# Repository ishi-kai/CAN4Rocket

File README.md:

# CAN Base Board for Rocket
CAN Base Board for Rocket.
The power supply section and the CAN communication section are insulated.

## Base System
This is a version with a universal board attached to the CAN base board.  
- [CAN_Isolation](./CAN_Isolation/)
- 

## Mini System
This is a mini version of the baseboard.  

- [CAN_Isolation_mini](./CAN_Isolation_mini/)
- [CAN_Isolation_mini_3.3V](./CAN_Isolation_mini_3.3V/)
- 

## High-Current Board for Servos System
This is a board with an XT60 connector for servos added to the mini version.  

- [CAN_Isolation_mini_XT60](./CAN_Isolation_mini_XT60/)
- [CAN_Isolation_mini_XT60_3.3V](./CAN_Isolation_mini_XT60_3.3V/)
-

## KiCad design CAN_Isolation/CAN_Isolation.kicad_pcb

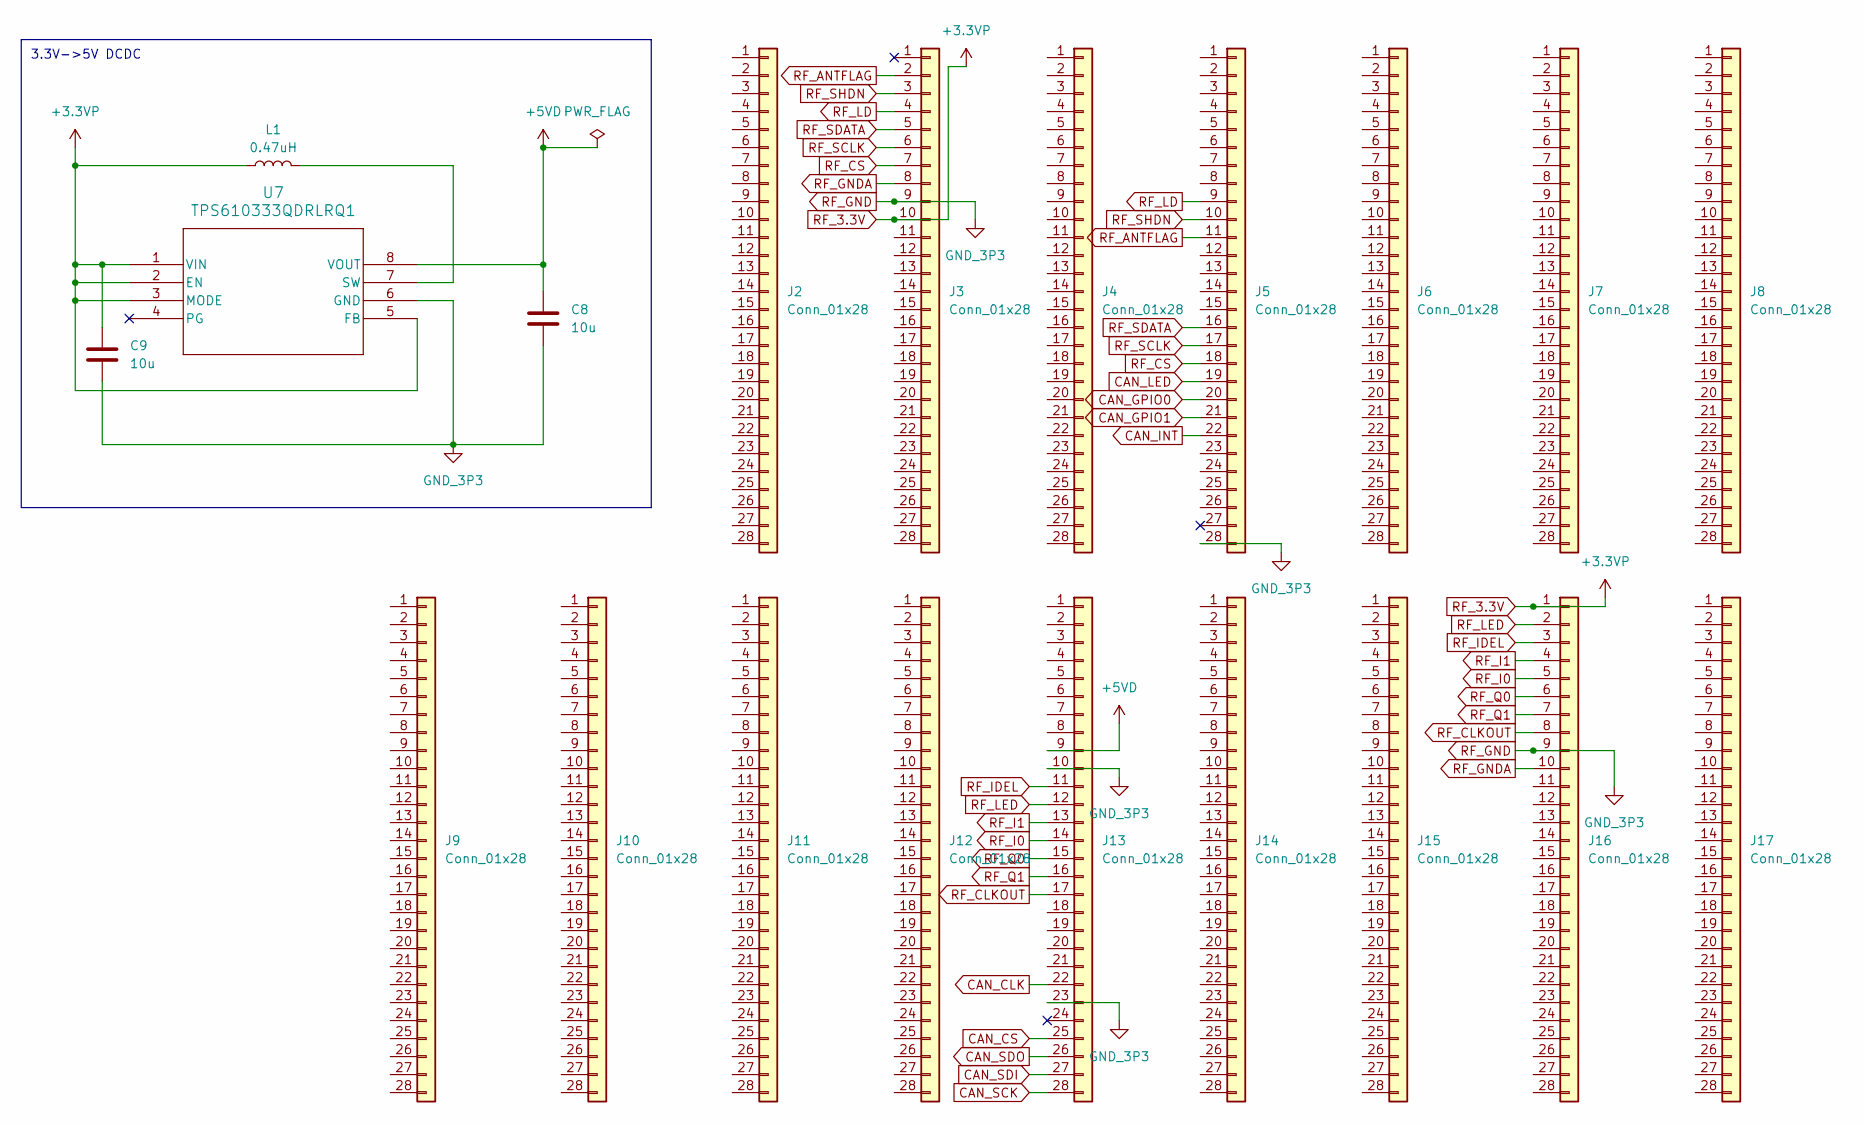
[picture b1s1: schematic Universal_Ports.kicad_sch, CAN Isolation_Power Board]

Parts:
C8, C9: 10u; C_0603_1608Metric
J2, J3, J4, J5, J6, J7, J8, J9, J10, J11, J12, J13, J14, J15, J16, J17: Conn_01x28; PinHeader_1x28_P2.54mm_NoSilkScreen
L1: 0.47uH; IND_LCCN_1608KK_TAY
U7: TPS610333QDRLRQ1; SOT-5X3-8_DRL_TEX

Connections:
+5VD: C8.1, J13.9, U7.8 (VOUT)
CAN_CLK: J13.22; also elsewhere on the board
CAN_CS: J13.25; also elsewhere on the board
CAN_GPIO0: J5.20; also elsewhere on the board
CAN_GPIO1: J5.21; also elsewhere on the board
CAN_INT: J5.22; also elsewhere on the board
CAN_LED: J5.19; also elsewhere on the board
CAN_SCK: J13.28; also elsewhere on the board
CAN_SDI: J13.27; also elsewhere on the board
CAN_SDO: J13.26; also elsewhere on the board
unnamed: L1.2, U7.7 (SW)
RF_3.3V: C9.1, J3.10, J16.1, L1.1, U7.1 (VIN), U7.2 (EN), U7.3 (MODE), U7.5 (FB); also elsewhere on the board
RF_ANTFLAG: J3.2, J5.11
RF_CLKOUT: J13.17, J16.8
RF_CS: J3.7, J5.18
RF_GND: C8.2, C9.2, J3.9, J5.28, J13.10, J13.23, J16.9, U7.6 (GND); also elsewhere on the board
RF_GNDA: J3.8, J16.10
RF_I0: J13.14, J16.5
RF_I1: J13.13, J16.4
RF_IDEL: J13.11, J16.3
RF_LD: J3.4, J5.9
RF_LED: J13.12, J16.2
RF_Q0: J13.15, J16.6
RF_Q1: J13.16, J16.7
RF_SCLK: J3.6, J5.17
RF_SDATA: J3.5, J5.16
RF_SHDN: J3.3, J5.10

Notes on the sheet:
3.3V->5V DCDC

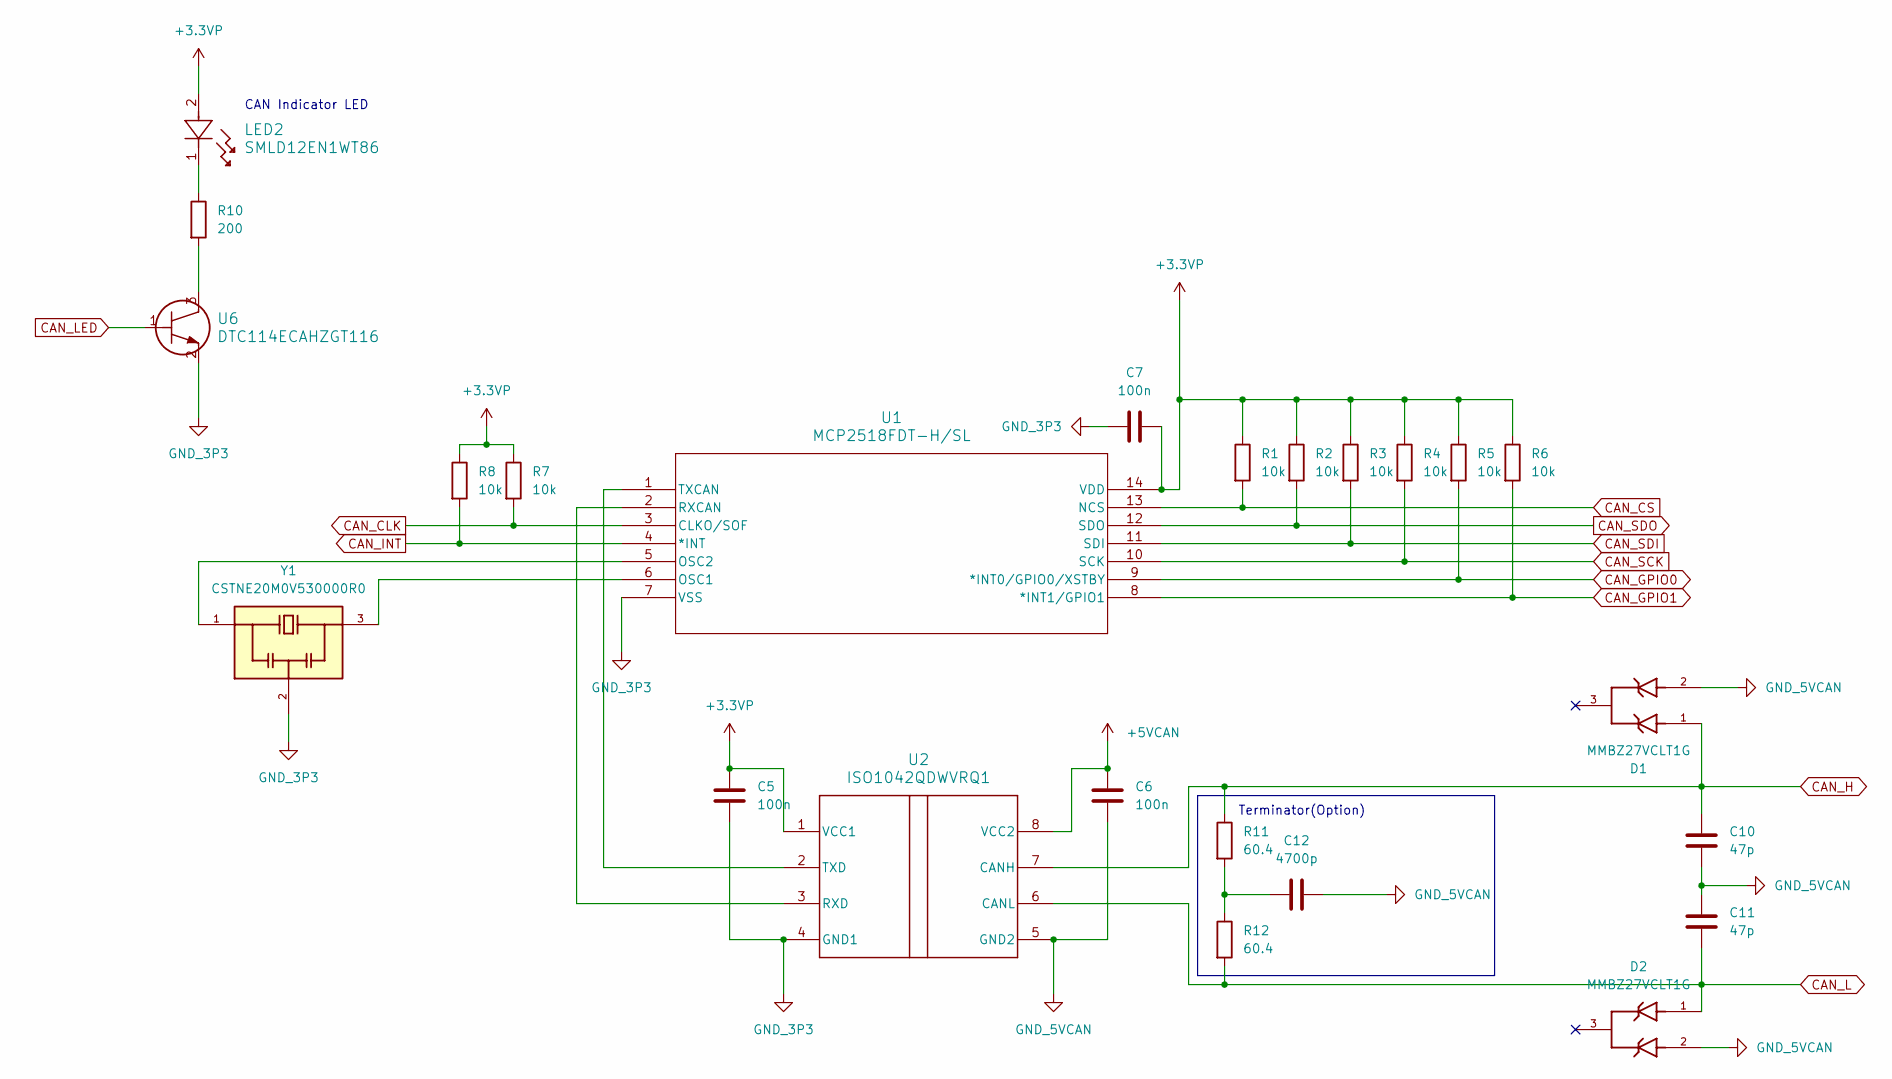
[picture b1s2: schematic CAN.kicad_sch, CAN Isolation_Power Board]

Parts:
C5, C6, C7: 100n; C_0603_1608Metric
C10, C11: 47p; C_0603_1608Metric
C12: 4700p; C_0603_1608Metric
D1, D2: MMBZ27VCLT1G; SOT95P237X111-3N; PARTREV 17
LED2: SMLD12EN1WT86
R1, R2, R3, R4, R5, R6, R7, R8: 10k; R_0603_1608Metric
R10: 200; R_0603_1608Metric
R11, R12: 60.4; R_Axial_DIN0207_L6.3mm_D2.5mm_P7.62mm_Horizontal
U1: MCP2518FDT-H/SL; SOIC14_150MIL_SL_MCH
U2: ISO1042QDWVRQ1; DWV0008A-IPC_A
U6: DTC114ECAHZGT116; TRANS_DTCZCAHZGT_ROM
Y1: CSTNE20M0V530000R0; OSC_CSTNE20M0V530000R0; PARTREV JGC42-8853B

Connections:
+5VCAN: C6.1, U2.8 (VCC2); also elsewhere on the board
CAN_CLK: R7.2, U1.3 (CLKO/SOF); also elsewhere on the board
CAN_CS: R1.2, U1.13 (NCS); also elsewhere on the board
CAN_GPIO0: R5.2, U1.9 (*INT0/GPIO0/XSTBY); also elsewhere on the board
CAN_GPIO1: R6.2, U1.8 (*INT1/GPIO1); also elsewhere on the board
CAN_H: C10.1, D1.1, R11.1, U2.7 (CANH); also elsewhere on the board
CAN_INT: R8.2, U1.4 (*INT); also elsewhere on the board
CAN_L: C11.2, D2.1, R12.2, U2.6 (CANL); also elsewhere on the board
CAN_LED: U6.1; also elsewhere on the board
CAN_SCK: R4.2, U1.10 (SCK); also elsewhere on the board
CAN_SDI: R3.2, U1.11 (SDI); also elsewhere on the board
CAN_SDO: R2.2, U1.12 (SDO); also elsewhere on the board
GND_5VCAN: C6.2, C10.2, C11.1, C12.2, D1.2, D2.2, U2.5 (GND2); also elsewhere on the board
unnamed: C12.1, R11.2, R12.1
unnamed: LED2.1, R10.1
unnamed: R10.2, U6.3
unnamed: U1.6 (OSC1), Y1.3
unnamed: U1.5 (OSC2), Y1.1
unnamed: U1.2 (RXCAN), U2.3 (RXD)
unnamed: U1.1 (TXCAN), U2.2 (TXD)
RF_3.3V: C5.1, C7.2, LED2.2, R1.1, R2.1, R3.1, R4.1, R5.1, R6.1, R7.1, R8.1, U1.14 (VDD), U2.1 (VCC1); also elsewhere on the board
RF_GND: C5.2, C7.1, U1.7 (VSS), U2.4 (GND1), U6.2, Y1.2; also elsewhere on the board

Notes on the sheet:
CAN Indicator LED
Terminator(Option)

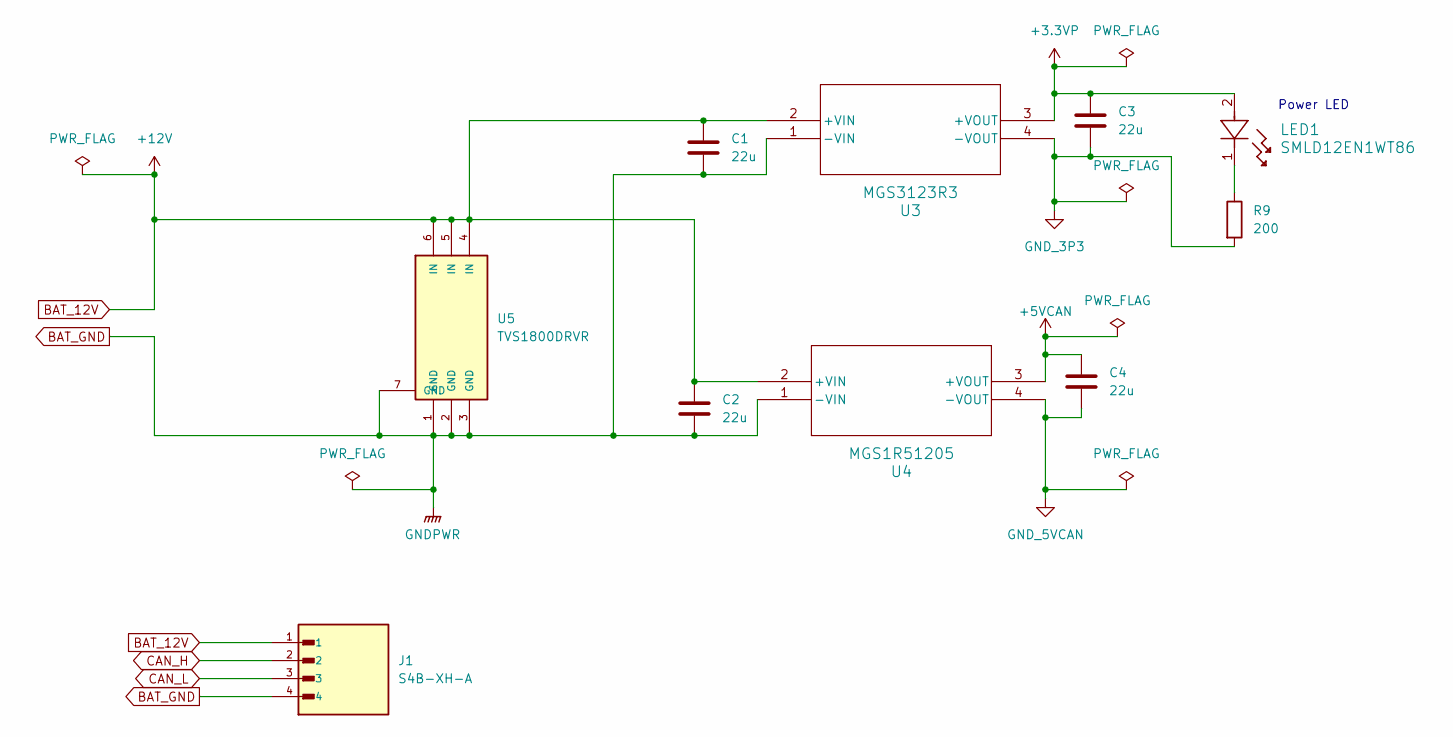
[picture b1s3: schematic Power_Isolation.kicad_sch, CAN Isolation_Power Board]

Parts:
C1, C2, C3, C4: 22u; C_1210_3225Metric
J1: S4B-XH-A; JST_S4B-XH-A
LED1: SMLD12EN1WT86
R9: 200; R_0603_1608Metric
U3: MGS3123R3; MGS3_COS
U4: MGS1R51205; MGS3_COS
U5: TVS1800DRVR; SON65P200X200X80-7N; PARTREV C

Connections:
+5VCAN: C4.1, U4.3 (+VOUT); also elsewhere on the board
BAT_12V: C1.1, C2.1, J1.1, U3.2 (+VIN), U4.2 (+VIN), U5.4 (IN), U5.5 (IN), U5.6 (IN)
BAT_GND: C1.2, C2.2, J1.4, U3.1 (-VIN), U4.1 (-VIN), U5.1 (GND), U5.2 (GND), U5.3 (GND), U5.7 (GND)
CAN_H: J1.2; also elsewhere on the board
CAN_L: J1.3; also elsewhere on the board
GND_5VCAN: C4.2, U4.4 (-VOUT); also elsewhere on the board
unnamed: LED1.1, R9.1
RF_3.3V: C3.1, LED1.2, U3.3 (+VOUT); also elsewhere on the board
RF_GND: C3.2, R9.2, U3.4 (-VOUT); also elsewhere on the board

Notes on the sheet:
Power LED

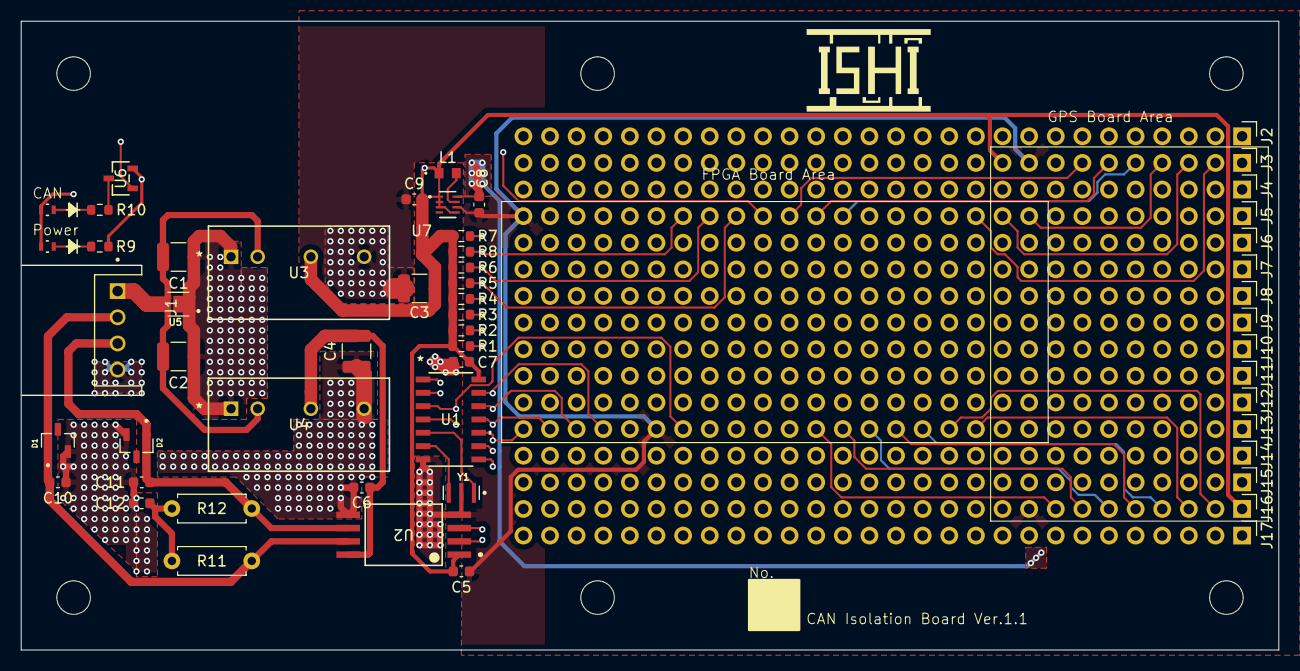
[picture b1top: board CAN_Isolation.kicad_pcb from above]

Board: 4 copper layers, 120.0 x 60.0 mm, 54 parts (0 on the bottom side), 41 nets.

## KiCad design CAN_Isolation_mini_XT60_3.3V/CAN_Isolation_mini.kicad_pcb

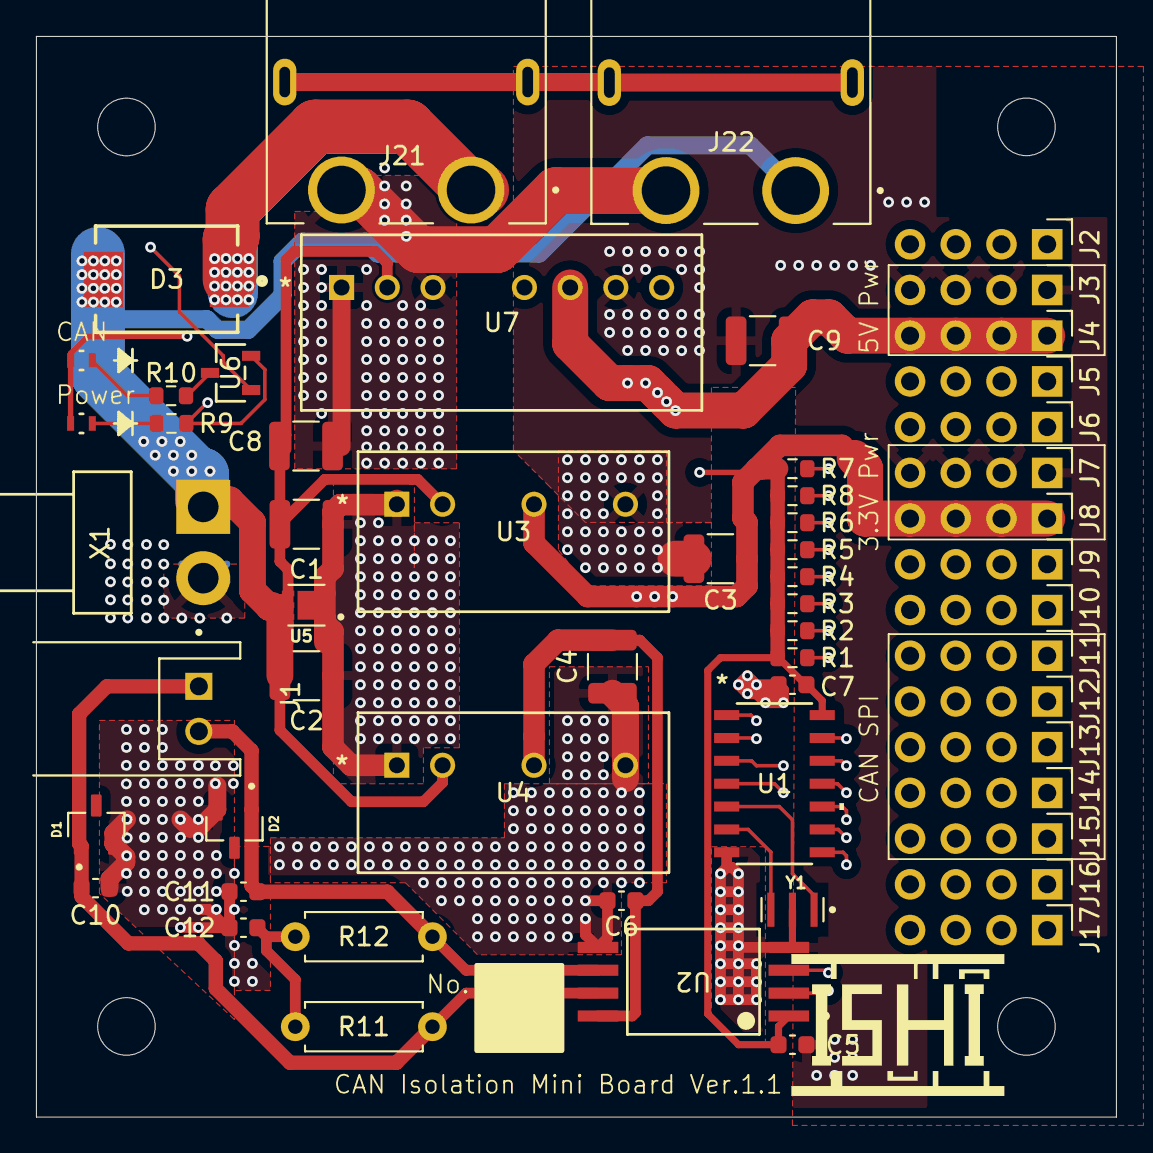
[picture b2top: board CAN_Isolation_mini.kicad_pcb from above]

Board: 4 copper layers, 60.0 x 60.0 mm, 57 parts (0 on the bottom side), 27 nets.

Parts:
C1, C2, C3, C4, C8, C9: 22u; C_1210_3225Metric
C5, C6, C7: 100n; C_0603_1608Metric
C10, C11: 47p; C_0603_1608Metric
C12: 4700p; C_0603_1608Metric
D1, D2: MMBZ27VCLT1G; SOT95P237X111-3N
D3: B520CQ-13-F; DIOM7959X250N
J1: S2B-XH-A; JST_S2B-XH-A
J2, J3, J4, J5, J6, J7, J8, J9, J10, J11, J12, J13, J14, J15, J16, J17: Conn_01x04_Pin; PinHeader_1x04_P2.54mm_Vertical_noSilk
J21, J22: XT60PW-F; AMASS_XT60PW-F
LED1, LED2: SMLD12EN1WT86
R1, R2, R3, R4, R5, R6, R7, R8: 10k; R_0603_1608Metric
R9, R10: 200; R_0603_1608Metric
R11, R12: 60.4; R_Axial_DIN0207_L6.3mm_D2.5mm_P7.62mm_Horizontal
U1: MCP2518FDT-H/SL; SOIC14_150MIL_SL_MCH
U2: ISO1042QDWVRQ1; DWV0008A-IPC_A
U3: MGS3123R3; MGS3_COS
U4: MGS1R51205; MGS3_COS
U5: TVS1800DRVR; SON65P200X200X80-7N
U6: DTC114ECAHZGT116; TRANS_DTCZCAHZGT_ROM
U7: MGS102405; SIP7_MGS10_COS
X1: B2PS-VH
Y1: CSTNE20M0V530000R0; OSC_CSTNE20M0V530000R0

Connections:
+3.3VP: C3.1, C5.1, C7.2, J8.1, J8.2, J8.3, J8.4, LED1.2, LED2.2, R1.1, R2.1, R3.1, R4.1, R5.1, R6.1, R7.1, R8.1, U1.14 (VDD), U2.1 (VCC1), U3.3 (+VOUT)
+5VCAN: C4.1, C6.1, U2.8 (VCC2), U4.3 (+VOUT)
+5VP: C9.1, J4.1, J4.2, J4.3, J4.4, U7.6 (+VOUT)
BAT_12V: C1.1, C2.1, C8.1, D3.A, J22.1, U3.2 (+VIN), U4.2 (+VIN), U5.4 (IN), U5.5 (IN), U5.6 (IN), U7.2 (+VIN), X1.1
BAT_GND: C1.2, C2.2, C8.2, J21.2, J21.S1 (SHIELD), J21.S2 (SHIELD), J22.2, J22.S1 (SHIELD), J22.S2 (SHIELD), U3.1 (-VIN), U4.1 (-VIN), U5.1 (GND), U5.2 (GND), U5.3 (GND), U5.7 (GND), U7.1 (-VIN), U7.3 (RC), X1.2
CAN_CLK: R7.2, U1.3 (CLKO/SOF)
CAN_CS: J12.1, J12.2, J12.3, J12.4, R1.2, U1.13 (NCS)
CAN_GPIO0: R5.2, U1.9 (*INT0/GPIO0/XSTBY)
CAN_GPIO1: R6.2, U1.8 (*INT1/GPIO1)
CAN_H: C10.1, D1.1, J1.1, R11.1, U2.7 (CANH)
CAN_INT: R8.2, U1.4 (*INT)
CAN_L: C11.2, D2.1, J1.2, R12.2, U2.6 (CANL)
CAN_LED: J11.1, J11.2, J11.3, J11.4, U6.1
CAN_SCK: J15.1, J15.2, J15.3, J15.4, R4.2, U1.10 (SCK)
CAN_SDI: J14.1, J14.2, J14.3, J14.4, R3.2, U1.11 (SDI)
CAN_SDO: J13.1, J13.2, J13.3, J13.4, R2.2, U1.12 (SDO)
GND_5VCAN: C4.2, C6.2, C10.2, C11.1, C12.2, D1.2, D2.2, U2.5 (GND2), U4.4 (-VOUT)
GND_VP: C3.2, C5.2, C7.1, C9.2, J3.1, J3.2, J3.3, J3.4, J7.1, J7.2, J7.3, J7.4, R9.2, U1.7 (VSS), U2.4 (GND1), U3.4 (-VOUT), U6.2, U7.7 (-VOUT), Y1.2
unnamed: C12.1, R11.2, R12.1
unnamed: D3.C, J21.1
unnamed: LED1.1, R9.1
unnamed: LED2.1, R10.1
unnamed: R10.2, U6.3
unnamed: U1.6 (OSC1), Y1.3
unnamed: U1.5 (OSC2), Y1.1
unnamed: U1.2 (RXCAN), U2.3 (RXD)
unnamed: U1.1 (TXCAN), U2.2 (TXD)

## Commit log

2026-02-16 1st commit.
    1st commit.
2026-02-16 Change name.
    Change name.
